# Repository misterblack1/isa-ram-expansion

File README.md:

# 8-bit ISA RAM expansion board with UMB support

This is my simple 8-bit ISA RAM expansion board. I created it to allow me to add UMB memory to a regular XT. It can also bring a 512k or 256k XT up to a full 640k.

- It is simple and easy to build.
- PCB is small so it is inexpensive to have produced.
- No drivers needed. (For conventional memory support)
- Desienged with KiCad, files available here. Free to modify.
- This card only supports conventional memory, no EMS. Extra RAM can be mapped into the high memory space (above 640k) allowing for UMB on XT machines.
- Required parts to build are marked on the PCB silk screen and on the schematic. (Sorry no BOM)

To access UBM, there are various DOS utilities to do this. I have a set of them uploaded in this REPO:
https://github.com/misterblack1/tandy1000ex-hx-ram/tree/master/umb_dos_utils

This card has 512k of 8-bit RAM on it. Therefore, you can map that 512k into the 8088 address space in 128k chunks. (Four chunks.) Use the DIP switches to select which banks are mapped by disabling the extra RAM on the ISA card. Even though you can map the 512k into all of the 1024k of address space in the 8088, please remember the mapping repeats once.

If you imagine the 512k chip is broken up into 4 banks of 128 k. A, B, C and D:

- A -> 0-128k (Lower)
- B -> 128k-256k (Lower)
- C -> 256k-320k (Lower)
- D -> 320k-512k (Lower)
- A -> 512k-640k (Upper)
- B -> 640k-768k (Upper)
- C -> 768k-897k (Upper)
- D -> 869-1024k (Upper)

So when configuring the card to map the 512k RAM into the system memory, you can only use any given bank on time. (Lower OR upper.) So, if you are using lower bank C and D to bring a PC from 256k to 512k total system RAM, you cannot use the upper bank C and D because they are already being used. If you do, the system will crash.

Example:

PC has 256k of RAM installed on the motherboard. This motherboard RAM wil exist from 0k to 256k. 
You want this ISA card to bring the system to 640k conventional. 

Memory map would look like this:

- A -> 0-128k Motherboard
- B -> 128k-256k Motherboard
- C -> 256k-320k ISA RAM card
- D -> 320k-512k ISA RAM card
- A -> 512k-640k ISA RAM card
- B -> 640k-768k used by CGA/MDA card
- C -> 768k-897k Unused
- D -> 869-1024k Unused and System ROMs

So to configure the card, you must configure the DIP switches to disable the ISA RAM card mapping into lower A and B and upper B and D. That way it does not overlap these parts of the system.

Set SW1, SW2, SW6, SW7 and SW8 to ON. The rest should be off. If you try to add UMB memory to upper bank C (768k to 897k) this will not work and cause a crash because you are already using lower bank C to expand from 256k to 320k. The only unused bank on this card would be B -- but you cannot use it for UMB because the 640k-768k range is typically used by the video card. (MDA, CDA, etc.)

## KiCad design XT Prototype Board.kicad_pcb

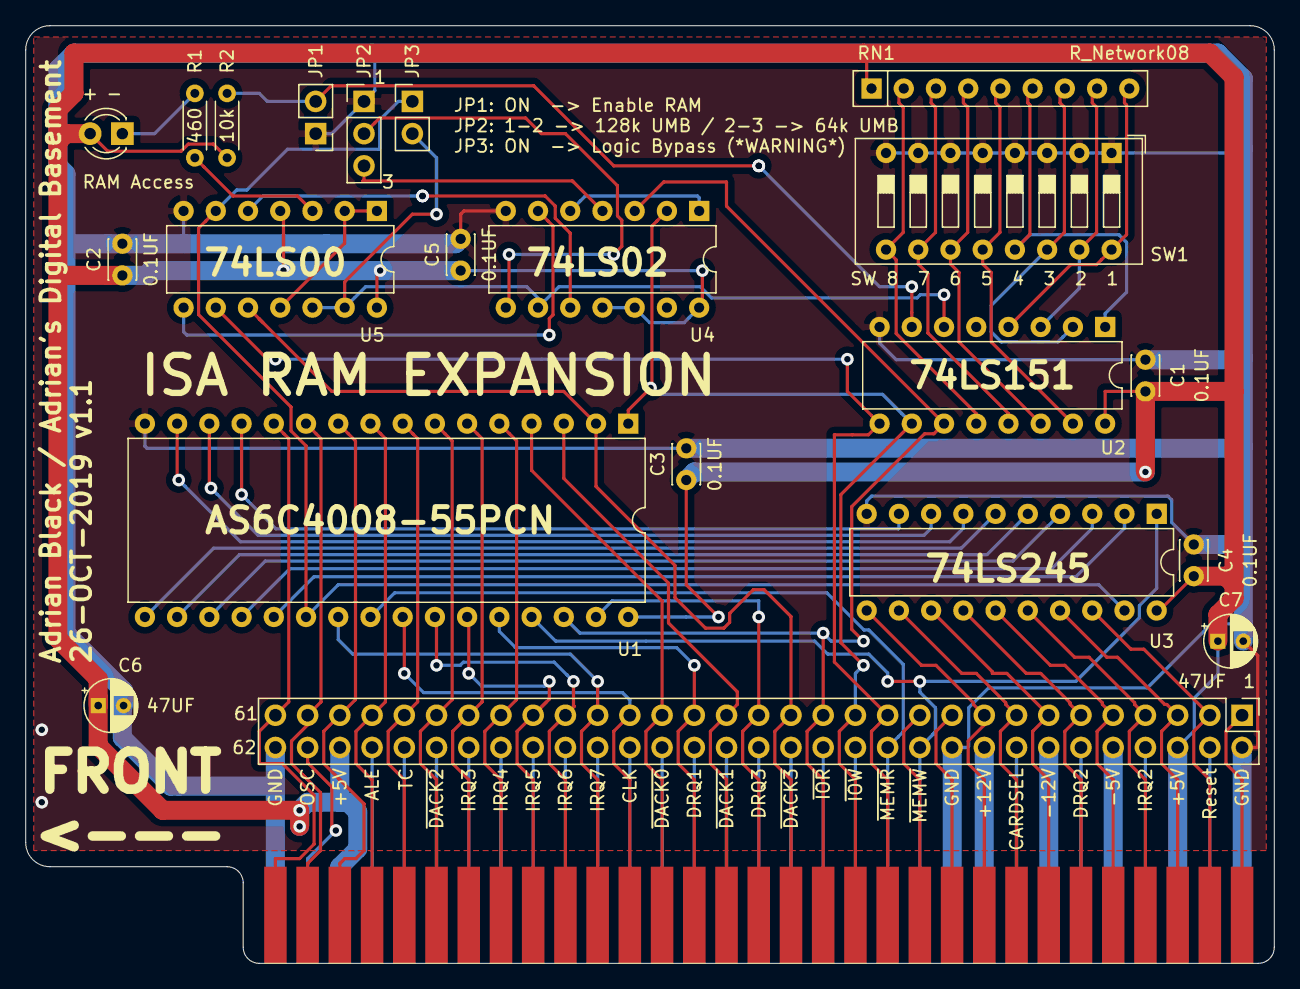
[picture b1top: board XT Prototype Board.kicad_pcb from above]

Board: 2 copper layers, 98.4 x 73.9 mm, 22 parts (0 on the bottom side), 86 nets.

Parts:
C1, C2, C3, C4, C5: 0.1UF; C_Disc_D3.0mm_W2.0mm_P2.50mm
C6, C7: 47UF; CP_Radial_D4.0mm_P2.00mm
J1: Bus_ISA_8bit; Conn_Edge_PCB_ISA8
J2: Breakout; PinHeader_2x31_P2.54mm_Vertical
JP1: Enable RAM; PinHeader_1x02_P2.54mm_Vertical
JP2: 128k / 64k UMB; PinHeader_1x03_P2.54mm_Vertical
JP3: Bypass Logic; PinHeader_1x02_P2.54mm_Vertical
R1: 460; R_Axial_DIN0204_L3.6mm_D1.6mm_P5.08mm_Horizontal
R2: 10k; R_Axial_DIN0204_L3.6mm_D1.6mm_P5.08mm_Horizontal
RAM Access: LED; LED_D3.0mm
RN1: R_Network08; R_Array_SIP9
SW1: SW_DIP_x08; SW_DIP_SPSTx08_Slide_9.78x22.5mm_W7.62mm_P2.54mm
U1: AS6C4008-55PCN; DIP-32_W15.24mm
U2: 74LS151; DIP-16_W7.62mm
U3: 74LS245; DIP-20_W7.62mm
U4: 74LS02; DIP-14_W7.62mm
U5: 74LS00; DIP-14_W7.62mm

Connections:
+5V: C1.1, C2.1, C3.1, C4.1, C5.1, C6.1, C7.1, J1.3, J1.29, J2.6, J2.58, R2.2, RAM Access.2, RN1.1, U1.32, U2.16, U3.20, U4.11, U4.12, U4.14, U5.4, U5.14
+12V: J1.9, J2.18
-5V: J1.5, J2.10
-12V: J1.7, J2.14
A0: J1.62, J2.61, U1.12
A1: J1.61, J2.59, U1.11
A2: J1.60, J2.57, U1.10
A3: J1.59, J2.55, U1.9
A4: J1.58, J2.53, U1.8
A5: J1.57, J2.51, U1.7
A6: J1.56, J2.49, U1.6
A7: J1.55, J2.47, U1.5
A8: J1.54, J2.45, U1.27
A9: J1.53, J2.43, U1.26
A10: J1.52, J2.41, U1.23
A11: J1.51, J2.39, U1.25
A12: J1.50, J2.37, U1.4
A13: J1.49, J2.35, U1.28
A14: J1.48, J2.33, U1.3
A15: J1.47, J2.31, U1.31
A16: J1.46, J2.29, U1.2, U5.10
A17: J1.45, J2.27, U1.30, U2.11, U4.3
A18: J1.44, J2.25, U1.1, U2.10, U4.2
A19: J1.43, J2.23, U2.9, U5.9
AEN: J1.42, J2.21
ALE: J1.28, J2.56
BD0: U1.13, U3.9
BD1: U1.14, U3.8
BD2: U1.15, U3.7
BD3: U1.17, U3.6
BD4: U1.18, U3.5
BD5: U1.19, U3.4
BD6: U1.20, U3.3
BD7: U1.21, U3.2
CARDSEL: J1.8, J2.16
CLK: J1.20, J2.40
D0: J1.40, J2.17, U3.11
D1: J1.39, J2.15, U3.12
D2: J1.38, J2.13, U3.13
D3: J1.37, J2.11, U3.14
D4: J1.36, J2.9, U3.15
D5: J1.35, J2.7, U3.16
D6: J1.34, J2.5, U3.17
D7: J1.33, J2.3, U3.18
DECODED_CS: JP3.2, U2.6, U4.9, U5.12, U5.13
DRQ1: J1.18, J2.36
DRQ2: J1.6, J2.12
DRQ3: J1.16, J2.32
GND: C1.2, C2.2, C3.2, C4.2, C5.2, C6.2, C7.2, J1.1, J1.10, J1.31, J2.2, J2.20, J2.62, JP1.1, JP2.1, SW1.1, SW1.2, SW1.3, SW1.4, SW1.5, SW1.6, SW1.7, SW1.8, U1.16, U2.8, U3.10, U4.7, U5.7
IOCHK: J1.32, J2.1
IORDY: J1.41, J2.19
IRQ2: J1.4, J2.8
IRQ3: J1.25, J2.50
IRQ4: J1.24, J2.48
IRQ5: J1.23, J2.46
IRQ6: J1.22, J2.44
IRQ7: J1.21, J2.42
unnamed: R1.2, RAM Access.1
unnamed: JP1.2, R2.1, U2.7
unnamed: JP2.2, U4.8
unnamed: JP2.3, U4.4
unnamed: R1.1, U5.3
unnamed: RN1.2, SW1.9, U2.12
unnamed: RN1.3, SW1.10, U2.13
unnamed: RN1.4, SW1.11, U2.14
unnamed: RN1.5, SW1.12, U2.15
unnamed: RN1.6, SW1.13, U2.1
unnamed: RN1.7, SW1.14, U2.2
unnamed: RN1.8, SW1.15, U2.3
unnamed: RN1.9, SW1.16, U2.4
unnamed: U4.1, U4.5
unnamed: U4.6, U5.8
unnamed: U4.10, U5.5
unnamed: U5.1, U5.2, U5.11
OSC: J1.30, J2.60
RESET: J1.2, J2.4
SRAM_CE: JP3.1, U1.22, U3.19, U5.6
TC: J1.27, J2.54
~DACK0: J1.19, J2.38
~DACK1: J1.17, J2.34
~DACK2: J1.26, J2.52
~DACK3: J1.15, J2.30
~IOR: J1.14, J2.28
~IOW: J1.13, J2.26
~MEMR: J1.12, J2.24, U1.24
~MEMW: J1.11, J2.22, U1.29, U3.1

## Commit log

2024-01-11 Adding BOM from DigiKey
    A CSV that can be uplaoded to DigiKey for easier ordering
